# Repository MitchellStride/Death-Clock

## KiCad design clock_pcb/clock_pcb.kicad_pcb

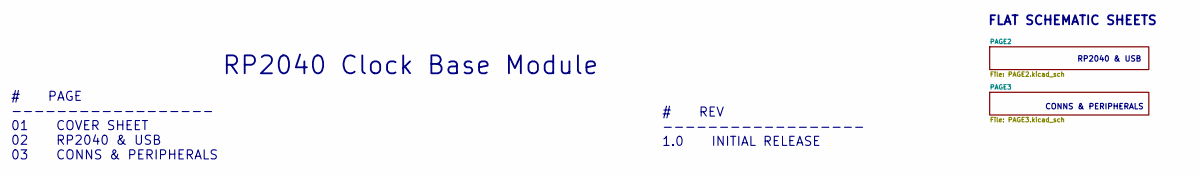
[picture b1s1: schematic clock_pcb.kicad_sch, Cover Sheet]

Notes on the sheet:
RP2040 & USB
FLAT SCHEMATIC SHEETS
RP2040 Clock Base Module
CONNS & PERIPHERALS
# REV ------------------ 1.0 INITIAL RELEASE
# PAGE ------------------ 01 COVER SHEET 02 RP2040 & USB 03 CONNS & PERIPHERALS

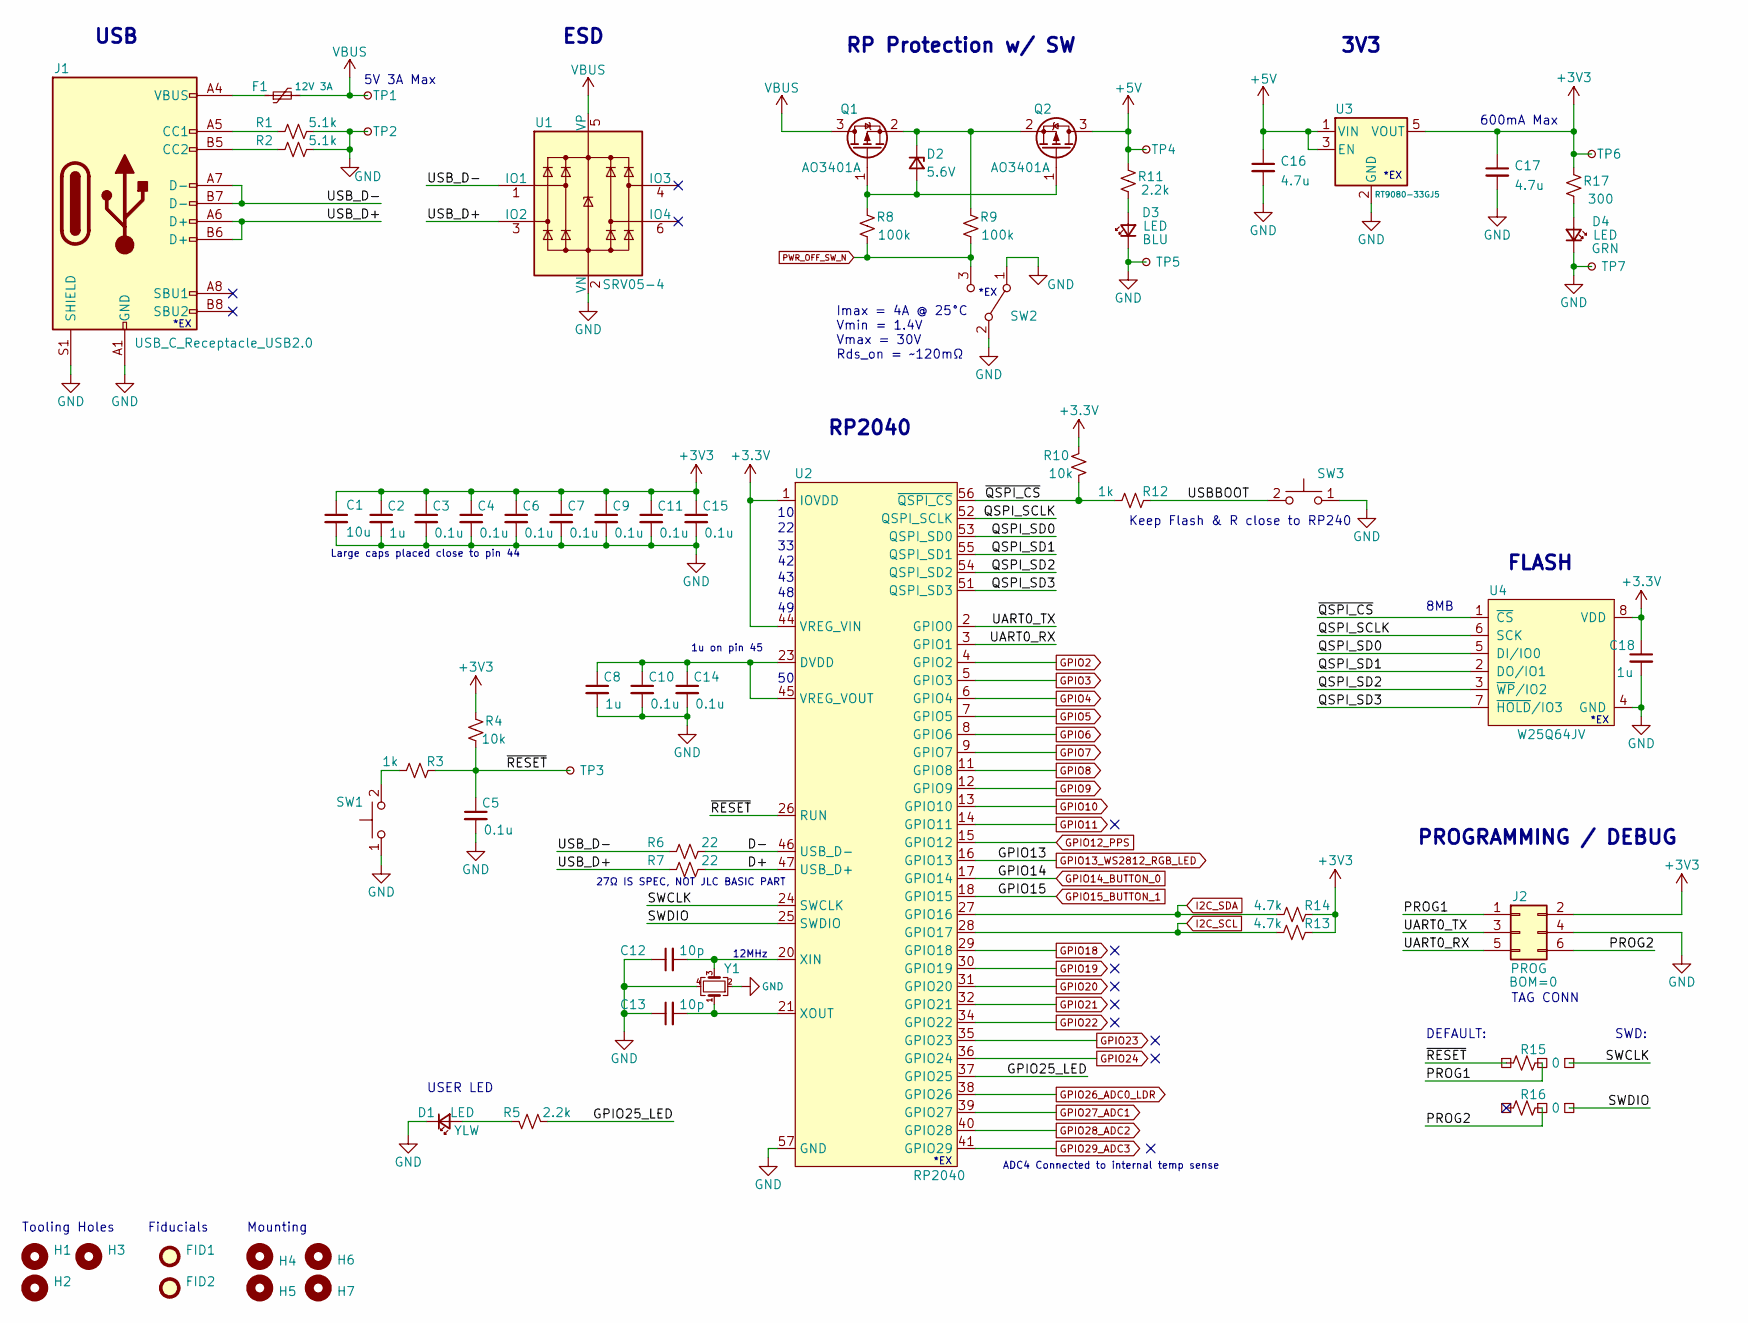
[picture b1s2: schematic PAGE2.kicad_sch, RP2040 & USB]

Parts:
C1: 10u; C_0402_1005Metric; lcsc C15525
C2, C8, C18: 1u; C_0402_1005Metric; lcsc C52923
C3, C4, C5, C6, C7, C9, C10, C11, C14, C15: 0.1u; C_0402_1005Metric; lcsc C1525
C12, C13: 10p; C_0402_1005Metric; lcsc C32949
C16, C17: 4.7u; C_0402_1005Metric; lcsc C23733
D1: LED; LED_0603_1608Metric; lcsc C72038
D2: 5.6V; D_MiniMELF; lcsc C8062
D3: LED; LED_0603_1608Metric; lcsc C72041
D4: LED; LED_0603_1608Metric; lcsc C72043
F1: 12V 3A; Fuse_1206_3216Metric; lcsc C516068
FID1, FID2: Fiducial; Fiducial_1mm_Mask2mm
H1, H2, H3: Tooling_Hole_JLC; JLC_Tooling_Hole
H4, H5, H6, H7: Mounting_Hole; MountingHole_2.7mm_M2.5
J1: USB_C_Receptacle_USB2.0; USB-C-16p; lcsc C167321
J2: PROG; Tag-Connect_TC2030-IDC-NL_2x03_P1.27mm_Vertical
Q1, Q2: AO3401A; SOT-23; lcsc C15127
R1, R2: 5.1k; R_0402_1005Metric; lcsc C25744
R3, R12: 1k; R_0402_1005Metric; lcsc C11702
R4, R10: 10k; R_0402_1005Metric; lcsc C25744
R5, R11: 2.2k; R_0402_1005Metric; lcsc C25879
R6, R7: 22; R_0402_1005Metric; lcsc C25092
R8, R9: 100k; R_0402_1005Metric; lcsc C25741
R13, R14: 4.7k; R_0402_1005Metric; lcsc C25900
R15, R16: 0; R_0402_1005Metric_3pad; lcsc C17168
R17: 300; R_0402_1005Metric; lcsc C25102
SW1, SW3: TS-1187A-B-A-B; SW_SPST_TL3342; lcsc C318884
SW2: SSSS811101; lcsc C109335
TP1: VBUS; TestPoint_Pad_D1.0mm
TP2: GND; TestPoint_Pad_D1.0mm
TP3: RST; TestPoint_Pad_D1.0mm
TP4, TP5, TP7: 5V; TestPoint_Pad_D1.0mm
TP6: 3V3; TestPoint_Pad_D1.0mm
U1: SRV05-4; SOT-23-6; lcsc C85364
U2: RP2040; QFN-56_EP_7x7_Pitch0.4mm; lcsc C2040
U3: RT9080-33GJ5; SOT-23-5; lcsc C841192
U4: W25Q64JV; WSON-8-1EP_4x4mm_P0.8mm_EP2.2x3mm; lcsc C2940195
Y1: XYDBPCNANF-12MHZ; Crystal_SMD_3225-4Pin_3.2x2.5mm; lcsc C9002

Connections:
+5V: C16.1, Q2.3 (D), R11.2, TP4.1, U3.1 (VIN), U3.3 (EN); also elsewhere on the board
/PAGE2/D+: R7.2, U2.47 (USB_D+)
/PAGE2/D-: R6.2, U2.46 (USB_D-)
/PAGE2/GPIO25_LED: R5.2, U2.37 (GPIO25)
/PAGE2/PROG1: J2.1, R15.2
/PAGE2/PROG2: J2.6, R16.2
/PAGE2/QSPI_SCLK: U2.52 (QSPI_SCLK), U4.6 (SCK)
/PAGE2/QSPI_SD0: U2.53 (QSPI_SD0), U4.5 (DI/IO0)
/PAGE2/QSPI_SD1: U2.55 (QSPI_SD1), U4.2 (DO/IO1)
/PAGE2/QSPI_SD2: U2.54 (QSPI_SD2), U4.3 (~WP/IO2)
/PAGE2/QSPI_SD3: U2.51 (QSPI_SD3), U4.7 (~HOLD/IO3)
/PAGE2/SWCLK: R15.3, U2.24 (SWCLK)
/PAGE2/SWDIO: R16.3, U2.25 (SWDIO)
/PAGE2/UART0_RX: J2.5, U2.3 (GPIO1)
/PAGE2/UART0_TX: J2.3, U2.2 (GPIO0)
/PAGE2/USBBOOT: R12.2, SW3.2
/PAGE2/USB_D+: J1.A6 (D+), J1.B6 (D+), R7.1, U1.3 (IO2)
/PAGE2/USB_D-: J1.A7 (D-), J1.B7 (D-), R6.1, U1.1 (IO1)
/PAGE2/~QSPI_CS: R10.2, R12.1, U2.56 (~QSPI_CS), U4.1 (~CS)
/PAGE2/~RESET: C5.1, R3.2, R4.2, R15.1, TP3.1, U2.26 (RUN)
GND: C1.2, C2.2, C3.2, C4.2, C5.2, C6.2, C7.2, C8.2, C9.2, C10.2, C11.2, C12.1, C13.1, C14.2, C15.2, C16.2, C17.2, C18.2, D1.1 (K), D3.1 (K), D4.1 (K), J1.A1 (GND), J1.A12 (GND), J1.B1 (GND), J1.B12 (GND), J1.S1 (SHIELD), J2.4, R1.2, R2.2, SW1.1, SW2.1 (A), SW2.2 (B), SW3.1, TP2.1, TP5.1, TP7.1, U1.2 (VN), U2.19 (TESTEN), U2.57 (GND), U3.2 (GND), U4.4 (GND), U4.9 (GND), Y1.2, Y1.4; also elsewhere on the board
GPIO2: U2.4 (GPIO2); also elsewhere on the board
GPIO3: U2.5 (GPIO3); also elsewhere on the board
GPIO4: U2.6 (GPIO4); also elsewhere on the board
GPIO5: U2.7 (GPIO5); also elsewhere on the board
GPIO6: U2.8 (GPIO6); also elsewhere on the board
GPIO7: U2.9 (GPIO7); also elsewhere on the board
GPIO8: U2.11 (GPIO8); also elsewhere on the board
GPIO9: U2.12 (GPIO9); also elsewhere on the board
GPIO10: U2.13 (GPIO10); also elsewhere on the board
GPIO11: U2.14 (GPIO11)
GPIO12_PPS: U2.15 (GPIO12)
GPIO13_WS2812_RGB_LED: U2.16 (GPIO13)
GPIO14_BUTTON_0: U2.17 (GPIO14)
GPIO15_BUTTON_1: U2.18 (GPIO15)
GPIO18: U2.29 (GPIO18)
GPIO19: U2.30 (GPIO19)
GPIO20: U2.31 (GPIO20)
GPIO21: U2.32 (GPIO21)
GPIO22: U2.34 (GPIO22)
GPIO23: U2.35 (GPIO23)
GPIO24: U2.36 (GPIO24)
GPIO26_ADC0_LDR: U2.38 (GPIO26); also elsewhere on the board
GPIO27_ADC1: U2.39 (GPIO27); also elsewhere on the board
GPIO28_ADC2: U2.40 (GPIO28); also elsewhere on the board
GPIO29_ADC3: U2.41 (GPIO29)
I2C_SCL: R13.1, U2.28 (GPIO17); also elsewhere on the board
I2C_SDA: R14.1, U2.27 (GPIO16); also elsewhere on the board
unnamed: C8.1, C10.1, C14.1, U2.23 (DVDD), U2.45 (VREG_VOUT), U2.50 (DVDD)
unnamed: C12.2, U2.20 (XIN), Y1.3
unnamed: C13.2, U2.21 (XOUT), Y1.1
unnamed: D1.2 (A), R5.1
unnamed: D2.1 (K), Q1.2 (S), Q2.2 (S), R9.1
unnamed: D2.2 (A), Q1.1 (G), Q2.1 (G), R8.1
unnamed: D3.2 (A), R11.1
unnamed: D4.2 (A), R17.1
unnamed: F1.1, J1.A4 (VBUS), J1.A9 (VBUS), J1.B4 (VBUS), J1.B9 (VBUS)
unnamed: J1.A5 (CC1), R1.1
unnamed: J1.B5 (CC2), R2.1
unnamed: R3.1, SW1.2
PWR_OFF_SW_N: R8.2, R9.2, SW2.3 (C); also elsewhere on the board
VBUS: F1.2, Q1.3 (D), TP1.1, U1.5 (VP); also elsewhere on the board

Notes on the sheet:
12MHz
5V 3A Max
3V3
8MB
*EX
Imax = 4A @ 25°C Vmin = 1.4V Vmax = 30V Rds_on = ~120mΩ
RP Protection w/ SW
27Ω IS SPEC, NOT JLC BASIC PART
Tooling Holes
ADC4 Connected to internal temp sense
ESD
Keep Flash & R close to RP240
USB
TAG CONN
Mounting
Large caps placed close to pin 44
FLASH
DEFAULT:
1u on pin 45
RP2040
600mA Max
USER LED
Fiducials
PROGRAMMING / DEBUG
SWD:

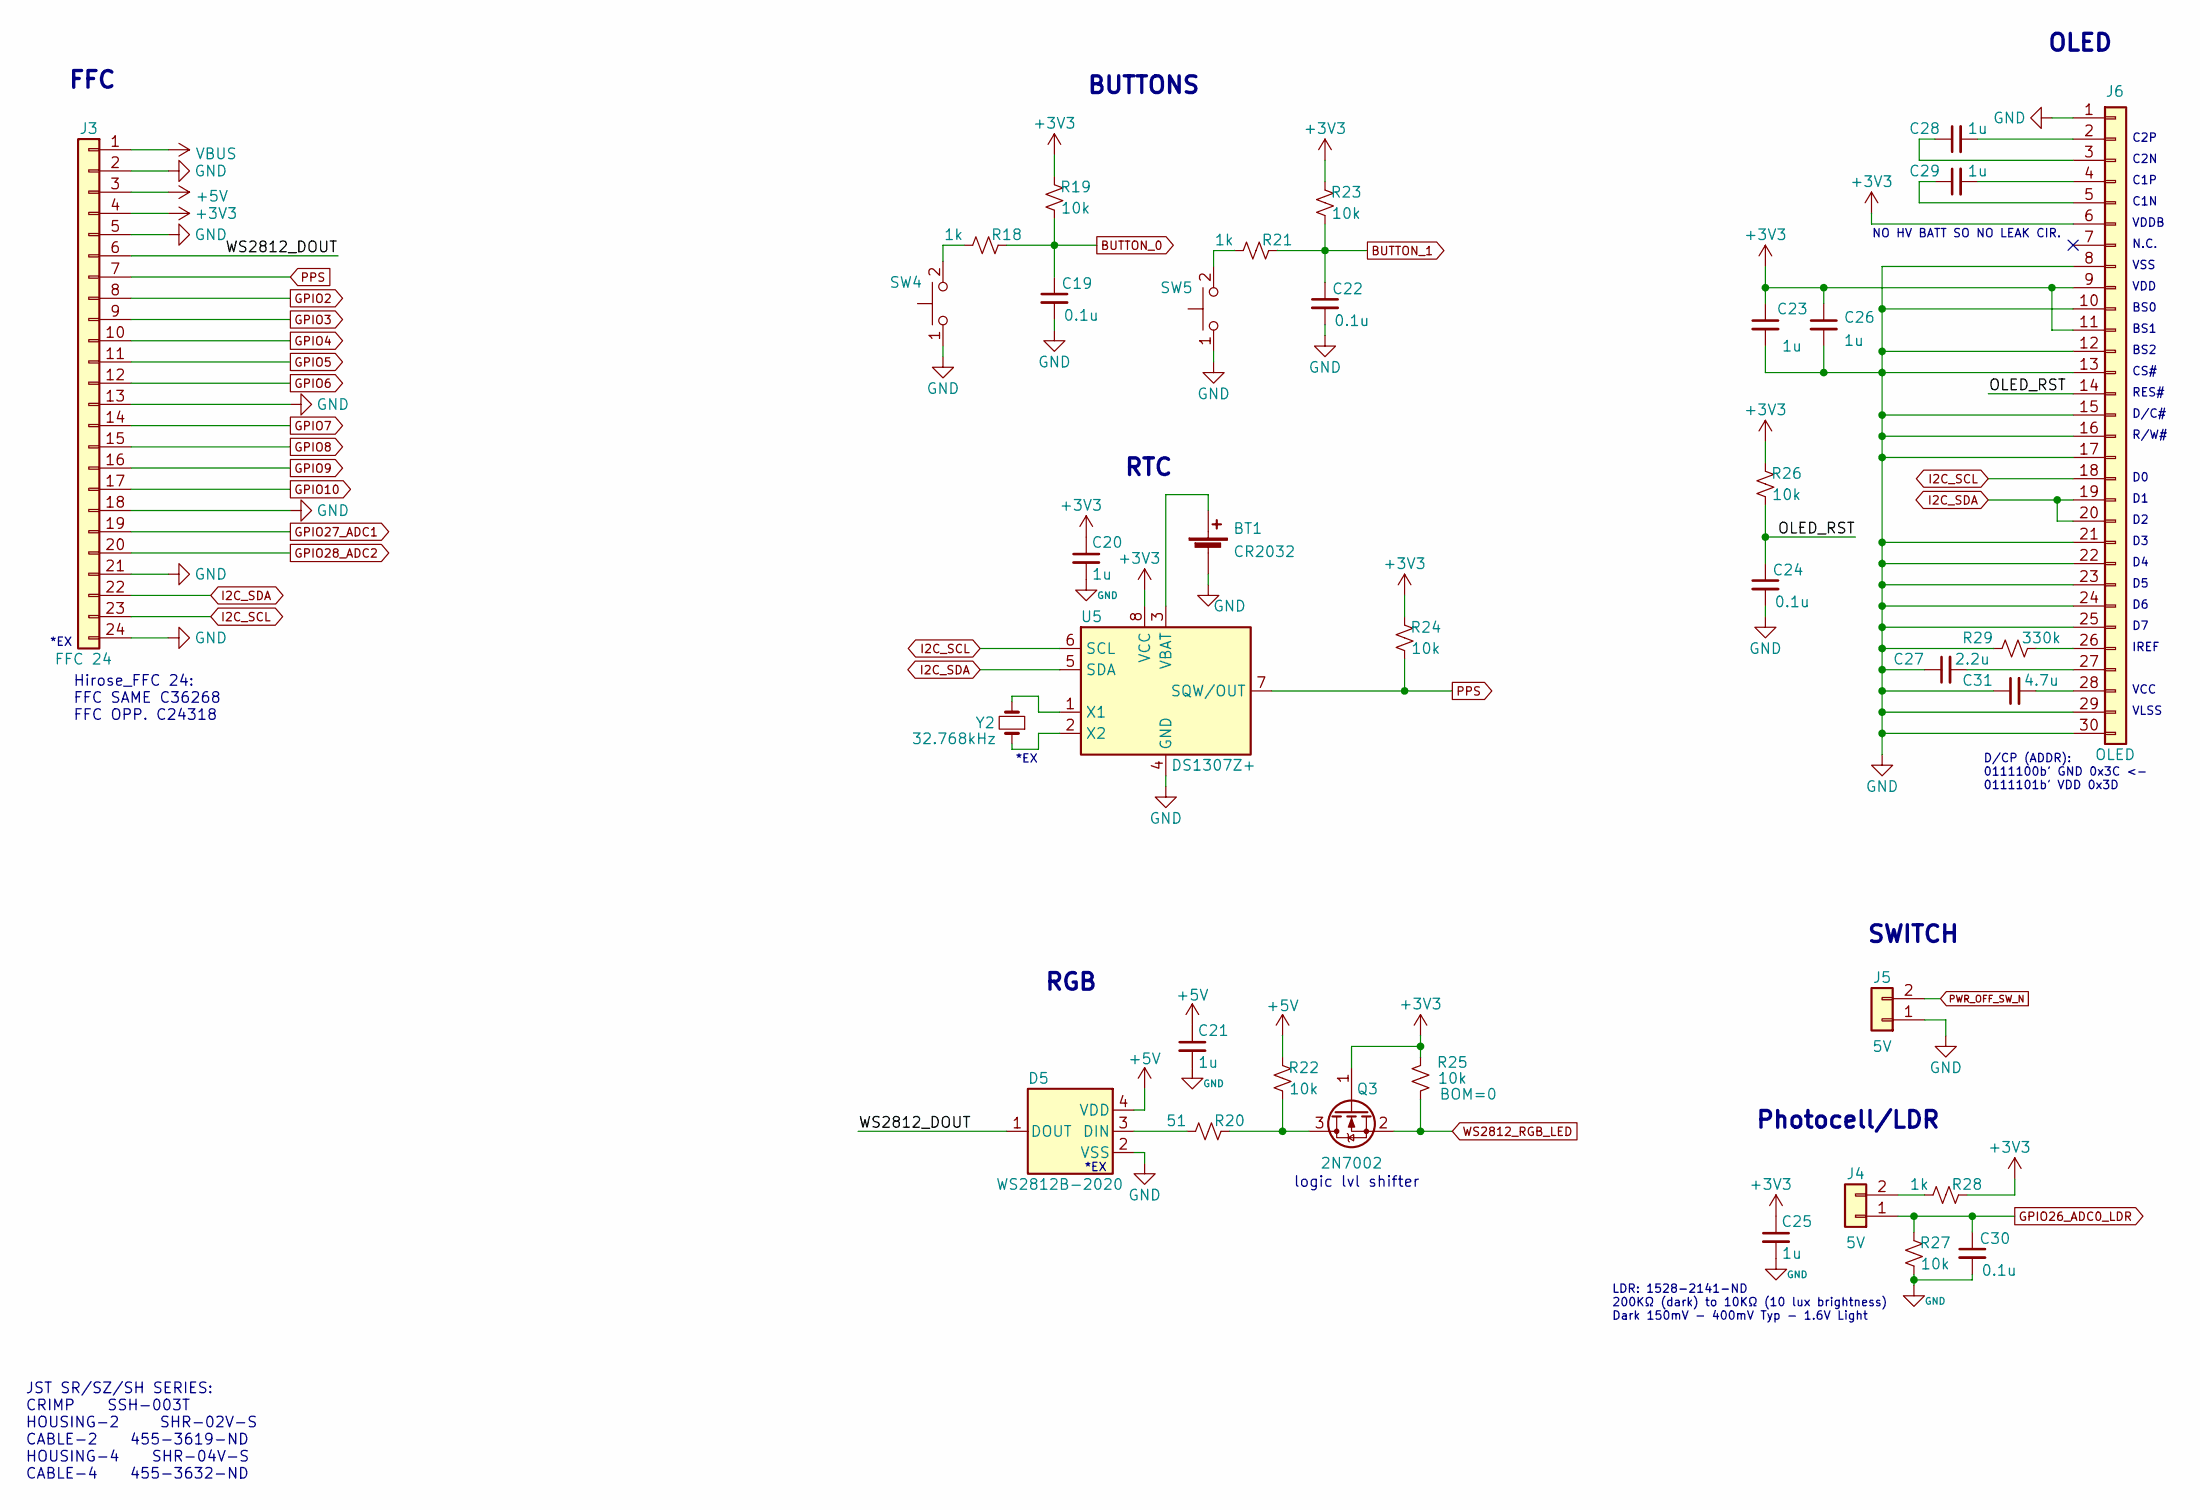
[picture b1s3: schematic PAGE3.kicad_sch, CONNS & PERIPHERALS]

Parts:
BT1: CR2032; Q&J_CR2032-BS-6-1; lcsc C70377
C19, C22, C24, C30: 0.1u; C_0402_1005Metric; lcsc C1525
C20, C21, C23, C25, C26, C28, C29: 1u; C_0402_1005Metric; lcsc C52923
C27: 2.2u; C_0402_1005Metric; lcsc C12530
C31: 4.7u; C_0402_1005Metric; lcsc C23733
D5: WS2812B-2020; lcsc C965555
J3: FFC 24; Hirose_FH12-24S-0.5SH_1x24-1MP_P0.50mm_Horizontal; lcsc C202112
J4, J5: 5V; JST_SH_SM02B-SRSS-TB_1x02-1MP_P1.00mm_Horizontal; lcsc C160402
J6: OLED; OLED-128O064D_edit; lcsc C2890596
Q3: 2N7002; SOT-23; lcsc C8545
R18, R21, R28: 1k; R_0402_1005Metric; lcsc C11702
R19, R22, R23, R24, R25, R26, R27: 10k; R_0402_1005Metric; lcsc C25744
R20: 51; R_0402_1005Metric; lcsc C25125
R29: 330k; R_0402_1005Metric; lcsc C25778
SW4, SW5: TS-1187A-B-A-B; SW_SPST_TL3342; lcsc C318884
U5: DS1307Z+; SOIC-8_3.9x4.9mm_P1.27mm; lcsc C8959
Y2: 32.768kHz; Crystal_SMD_3215-2Pin_3.2x1.5mm; lcsc C95361

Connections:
+5V: C21.1, D5.4 (VDD), J3.3, R22.1; also elsewhere on the board
/PAGE3/OLED_RST: C24.1, J6.14, R26.2
/PAGE3/WS2812_DOUT: D5.1 (DOUT), J3.6
BUTTON_0: C19.1, R18.2, R19.2
BUTTON_1: C22.1, R21.2, R23.2
GND: BT1.2 (-), C19.2, C20.2, C21.2, C22.2, C23.2, C24.2, C25.2, C26.2, C27.1, C30.2, C31.1, D5.2 (VSS), J3.2, J3.5, J3.13, J3.18, J3.21, J3.24, J5.1, J6.1, J6.8, J6.10, J6.12, J6.13, J6.15, J6.16, J6.17, J6.21, J6.22, J6.23, J6.24, J6.25, J6.29, J6.30, R27.2, R29.1, SW4.1, SW5.1, U5.4 (GND); also elsewhere on the board
GPIO2: J3.8; also elsewhere on the board
GPIO3: J3.9; also elsewhere on the board
GPIO4: J3.10; also elsewhere on the board
GPIO5: J3.11; also elsewhere on the board
GPIO6: J3.12; also elsewhere on the board
GPIO7: J3.14; also elsewhere on the board
GPIO8: J3.15; also elsewhere on the board
GPIO9: J3.16; also elsewhere on the board
GPIO10: J3.17; also elsewhere on the board
GPIO26_ADC0_LDR: C30.1, J4.1, R27.1; also elsewhere on the board
GPIO27_ADC1: J3.19; also elsewhere on the board
GPIO28_ADC2: J3.20; also elsewhere on the board
I2C_SCL: J3.23, J6.18, U5.6 (SCL); also elsewhere on the board
I2C_SDA: J3.22, J6.19, J6.20, U5.5 (SDA); also elsewhere on the board
unnamed: BT1.1 (+), U5.3 (VBAT)
unnamed: C27.2, J6.27
unnamed: C28.1, J6.3
unnamed: C28.2, J6.2
unnamed: C29.1, J6.5
unnamed: C29.2, J6.4
unnamed: C31.2, J6.28
unnamed: D5.3 (DIN), R20.1
unnamed: J4.2, R28.1
unnamed: J6.26, R29.2
unnamed: Q3.3 (D), R20.2, R22.2
unnamed: R18.1, SW4.2
unnamed: R21.1, SW5.2
unnamed: U5.1 (X1), Y2.2
unnamed: U5.2 (X2), Y2.1
PPS: J3.7, R24.2, U5.7 (SQW/OUT)
PWR_OFF_SW_N: J5.2; also elsewhere on the board
VBUS: J3.1; also elsewhere on the board
WS2812_RGB_LED: Q3.2 (S), R25.2

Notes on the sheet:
VCC
BS2
OLED
*EX
SWITCH
RES#
R/W#
C1N
CS#
Photocell/LDR
NO HV BATT SO NO LEAK CIR.
logic lvl shifter
BS1
FFC
IREF
D/CP (ADDR): 0111100b' GND 0x3C <- 0111101b' VDD 0x3D
D/C#
VDDB
BS0
C2N
RTC
C1P
BUTTONS
LDR: 1528-2141-ND 200KΩ (dark) to 10KΩ (10 lux brightness) Dark 150mV - 400mV Typ - 1.6V Light
Hirose_FFC 24: FFC SAME C36268 FFC OPP. C24318
VLSS
VSS
C2P
JST SR/SZ/SH SERIES: CRIMP SSH-003T HOUSING-2 SHR-02V-S CABLE-2 455-3619-ND HOUSING-4 SHR-04V-S CABLE-4 455-3632-ND
N.C.
RGB
VDD

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
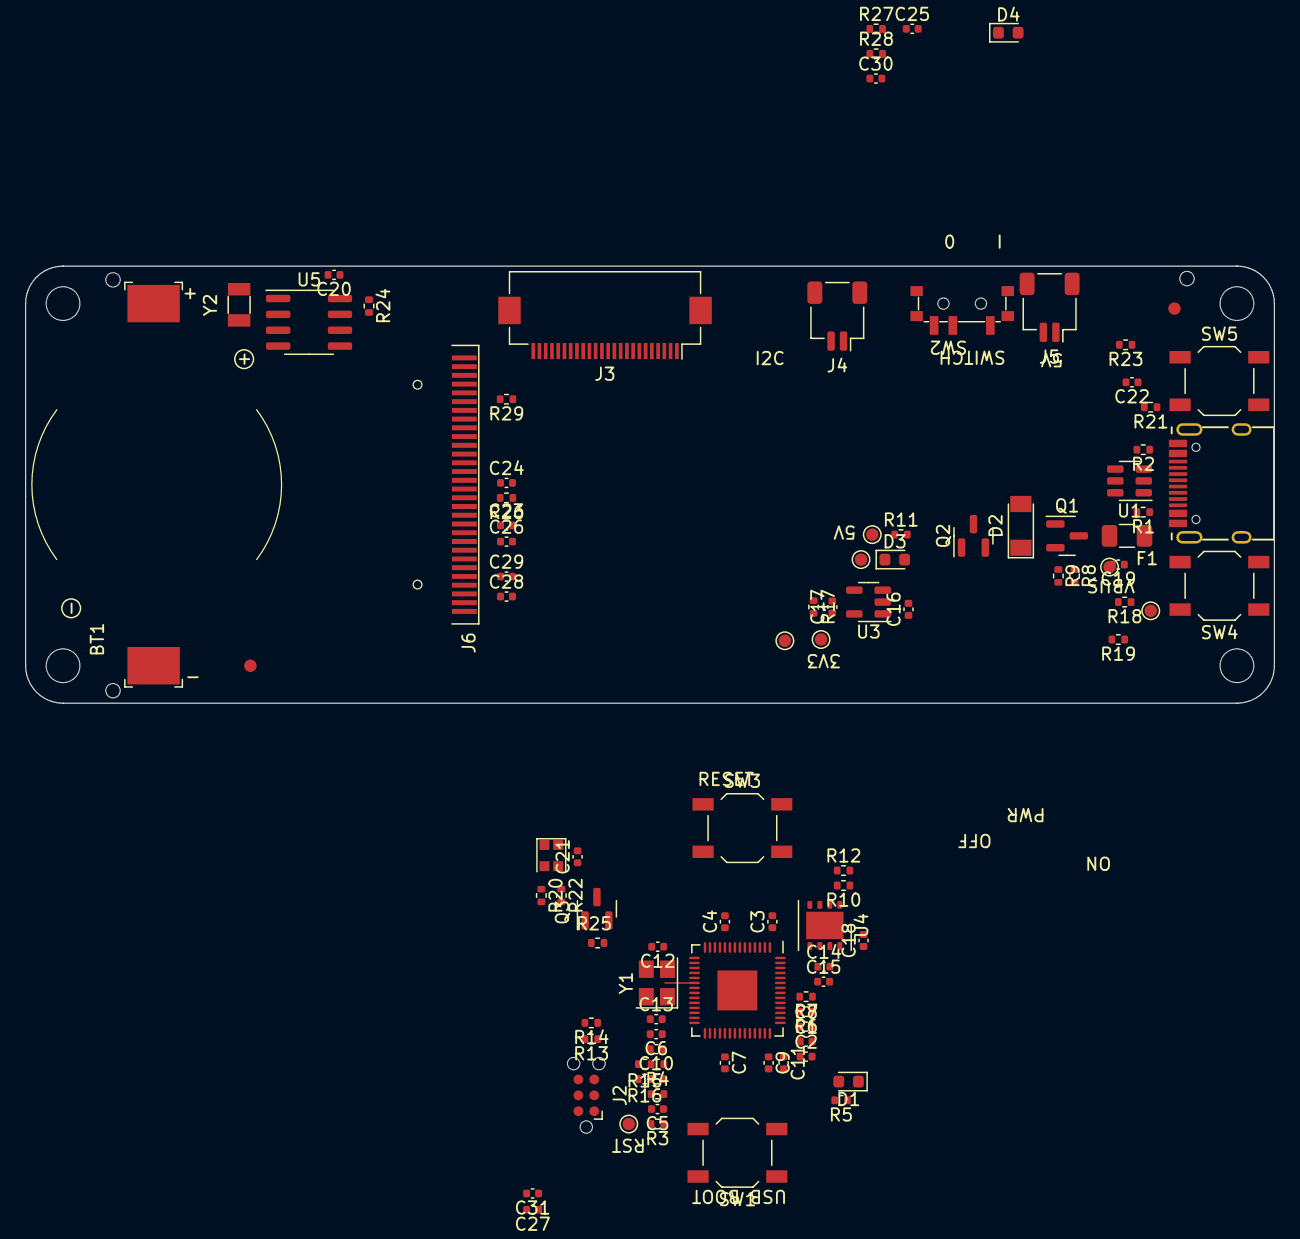
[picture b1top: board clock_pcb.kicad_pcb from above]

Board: 2 copper layers, 100.0 x 35.0 mm, 104 parts (0 on the bottom side), 71 nets.

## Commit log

2022-05-03 cleaned up and added rp2040
2022-12-10 break
2023-04-19 only brick nogging usbc left to add
2023-04-19 split clock out
